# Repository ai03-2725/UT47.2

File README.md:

# UT47.2
Hot-swappable 40% Keyboard PCB

#### In light of recent claims that I am 100% liable for any of my open source PCBs, I am adding this disclaimer.
#### I provide these PCBs as a reference for designing keyboard PCBs. Using them within your projects will require a will to do research of one's own and to learn the workings of them, potentially fixing issues if they exist.
# I provide these PCBs without liability and without any guarantees regarding functionality, as expressed in the MIT license under which all of these PCBs are licensed.

Keyboard Layout Editor layout: [Layout](http://www.keyboard-layout-editor.com/#/gists/ddc8fda154c2c93ac26e38cd5da5988e)

An open-source commission for [KeyHive](https://keyhive.xyz/).

The design is inspired by 40percent.club's Gnap keyboard, which is licensed under [CC BY-SA 4.0](https://creativecommons.org/licenses/by-sa/4.0/).

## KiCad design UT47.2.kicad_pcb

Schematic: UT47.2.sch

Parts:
C1, C2: 22p; C_0603
C3: 1uF; C_0603
C4, C5: 0.1u; C_0603
C6: 4.7u; C_0603
CR1, CR2, CR3, CR4, CR5, CR6, CR7, CR8: 0.1u; C_0603
F1: 500mA; Fuse_SMD1206_Reflow
R1, R5: 10k; R_0603
R2, R3: 22; R_0603
R4, R6: 5.1k; R_0603
RGB1, RGB2, RGB3, RGB4, RGB5, RGB6, RGB7, RGB8: WS2812B
SW1: SW_PUSH; SKQG-1155865
U1: ATMEGA32U2-AU; QFN-32-1EP_5x5mm_Pitch0.5mm
U2: PRTR5V0U2X; SOT143B
USB1: HRO-TYPE-C-31-M-12; HRO-TYPE-C-31-M-12-Assembly
Y1: 16MHz; Crystal_SMD_3225-4pin_3.2x2.5mm

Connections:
+5V: C4.1, C5.1, C6.1, CR1.1, CR2.1, CR3.1, CR4.1, CR5.1, CR6.1, CR7.1, CR8.1, F1.1, R1.1, RGB1.1 (VCC), RGB2.1 (VCC), RGB3.1 (VCC), RGB4.1 (VCC), RGB5.1 (VCC), RGB6.1 (VCC), RGB7.1 (VCC), RGB8.1 (VCC), U1.4 (VCC), U1.31 (UVCC), U1.32 (AVCC)
COL0: U1.26 ((PCINT10)PC4); also elsewhere on the board
COL1: U1.25 ((PCINT9/OC.1B)PC5); also elsewhere on the board
COL2: U1.21 ((PCINT7/OC.0A/OC.1C)PB7); also elsewhere on the board
COL3: U1.20 ((PCINT6)PB6); also elsewhere on the board
COL4: U1.19 ((PCINT5)PB5); also elsewhere on the board
COL5: U1.18 ((T1/PCINT4)PB4); also elsewhere on the board
COL6: U1.17 ((PD0/MISO/PCINT3)PB3); also elsewhere on the board
COL7: U1.16 ((PDI/MOSI/PCINT2)PB2); also elsewhere on the board
COL8: U1.15 ((SCLK/PCINT1)PB1); also elsewhere on the board
COL9: U1.14 ((~SS~/PCINT0)PB0); also elsewhere on the board
COL10: U1.12 ((~RTS~/AIN5/INT6)PD6); also elsewhere on the board
COL11: U1.11 ((XCK/AIN4/PCINT12)PD5); also elsewhere on the board
D+: R3.2, U1.29 (D+)
D-: R2.1, U1.30 (D-)
GND: C1.2, C2.2, C3.2, C4.2, C5.2, C6.2, CR1.2, CR2.2, CR3.2, CR4.2, CR5.2, CR6.2, CR7.2, CR8.2, R4.2, R5.1, R6.2, RGB1.3 (GND), RGB2.3 (GND), RGB3.3 (GND), RGB4.3 (GND), RGB5.3 (GND), RGB6.3 (GND), RGB7.3 (GND), RGB8.3 (GND), SW1.1, U1.3 (GND), U1.28 (UGND), U2.1, USB1.1, USB1.12, USB1.13, Y1.2, Y1.4
unnamed: C1.1, U1.1 (XTAL1), Y1.1
unnamed: C2.1, U1.2 (PC0(XTAL2)), Y1.3
unnamed: C3.1, U1.27 (UCAP)
unnamed: R1.2, SW1.2, U1.24 (PC1(~RESET~/dW))
unnamed: R2.2, U2.3, USB1.5, USB1.7
unnamed: R3.1, U2.2, USB1.6, USB1.8
unnamed: R4.1, USB1.10
unnamed: R5.2, U1.13 ((~CTS~/~HWB~/AIN6/T0/INT7)PD7)
unnamed: R6.1, USB1.4
unnamed: RGB1.2 (DOUT), RGB2.4 (DIN)
unnamed: RGB2.2 (DOUT), RGB3.4 (DIN)
unnamed: RGB3.2 (DOUT), RGB4.4 (DIN)
unnamed: RGB4.2 (DOUT), RGB5.4 (DIN)
unnamed: RGB5.2 (DOUT), RGB6.4 (DIN)
unnamed: RGB6.2 (DOUT), RGB7.4 (DIN)
unnamed: RGB7.2 (DOUT), RGB8.4 (DIN)
RGBLED: RGB1.4 (DIN), U1.23 ((OC.1A/PCINT8)PC6)
ROW0: U1.7 ((AIN0/INT1)PD1); also elsewhere on the board
ROW1: U1.8 ((RXD1/AIN1/INT2)PD2); also elsewhere on the board
ROW2: U1.9 ((TXD1/INT3)PD3); also elsewhere on the board
ROW3: U1.10 ((INT5/AIN3)PD4); also elsewhere on the board
VCC: F1.2, U2.4, USB1.2, USB1.11

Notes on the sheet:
Mir Keyboard
2018-11-28
1.0

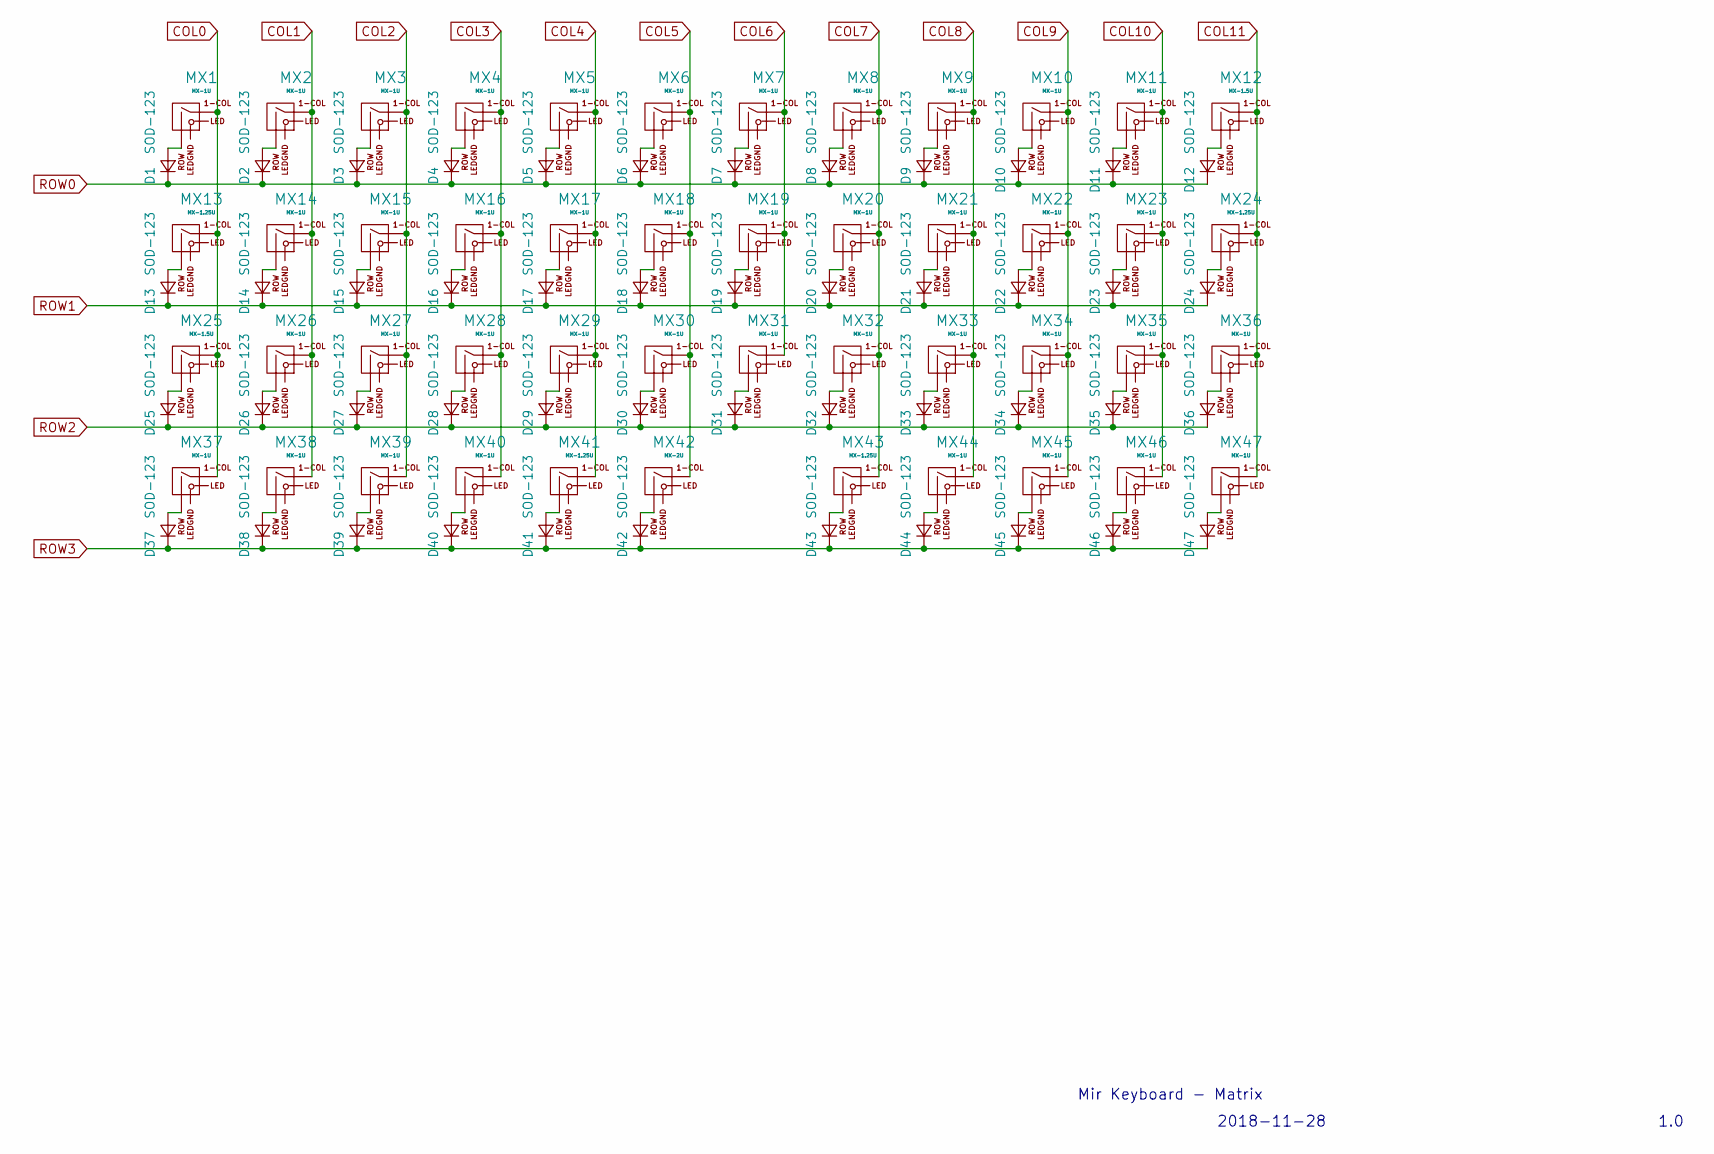
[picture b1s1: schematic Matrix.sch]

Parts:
D1, D2, D3, D4, D5, D6, D7, D8, D9, D10, D11, D12, D13, D14, D15, D16, D17, D18, D19, D20, D21, D22, D23, D24, D25, D26, D27, D28, D29, D30, D31, D32, D33, D34, D35, D36, D37, D38, D39, D40, D41, D42, D43, D44, D45, D46, D47: SOD-123; D_SOD-123
MX1, MX2, MX3, MX4, MX5, MX6, MX7, MX8, MX9, MX10, MX11, MX14, MX15, MX16, MX17, MX18, MX19, MX20, MX21, MX22, MX23, MX26, MX27, MX28, MX29, MX30, MX31, MX32, MX33, MX34, MX35, MX36, MX37, MX38, MX39, MX40, MX44, MX45, MX46, MX47: MX-1U; MXOnly-1U-Hotswap
MX12, MX25: MX-1.5U; MXOnly-1.5U-Hotswap
MX13, MX24, MX41, MX43: MX-1.25U; MXOnly-1.25U-Hotswap
MX42: MX-2U; MXOnly-2U-Hotswap-ReversedStabilizers

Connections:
COL0: MX1.1 (COL), MX13.1 (COL), MX25.1 (COL), MX37.1 (COL); also elsewhere on the board
COL1: MX2.1 (COL), MX14.1 (COL), MX26.1 (COL), MX38.1 (COL); also elsewhere on the board
COL2: MX3.1 (COL), MX15.1 (COL), MX27.1 (COL), MX39.1 (COL); also elsewhere on the board
COL3: MX4.1 (COL), MX16.1 (COL), MX28.1 (COL), MX40.1 (COL); also elsewhere on the board
COL4: MX5.1 (COL), MX17.1 (COL), MX29.1 (COL), MX41.1 (COL); also elsewhere on the board
COL5: MX6.1 (COL), MX18.1 (COL), MX30.1 (COL), MX42.1 (COL); also elsewhere on the board
COL6: MX7.1 (COL), MX19.1 (COL), MX31.1 (COL); also elsewhere on the board
COL7: MX8.1 (COL), MX20.1 (COL), MX32.1 (COL), MX43.1 (COL); also elsewhere on the board
COL8: MX9.1 (COL), MX21.1 (COL), MX33.1 (COL), MX44.1 (COL); also elsewhere on the board
COL9: MX10.1 (COL), MX22.1 (COL), MX34.1 (COL), MX45.1 (COL); also elsewhere on the board
COL10: MX11.1 (COL), MX23.1 (COL), MX35.1 (COL), MX46.1 (COL); also elsewhere on the board
COL11: MX12.1 (COL), MX24.1 (COL), MX36.1 (COL), MX47.1 (COL); also elsewhere on the board
unnamed: D1.2 (A), MX1.2 (ROW)
unnamed: D2.2 (A), MX2.2 (ROW)
unnamed: D3.2 (A), MX3.2 (ROW)
unnamed: D4.2 (A), MX4.2 (ROW)
unnamed: D5.2 (A), MX5.2 (ROW)
unnamed: D6.2 (A), MX6.2 (ROW)
unnamed: D7.2 (A), MX7.2 (ROW)
unnamed: D8.2 (A), MX8.2 (ROW)
unnamed: D9.2 (A), MX9.2 (ROW)
unnamed: D10.2 (A), MX10.2 (ROW)
unnamed: D11.2 (A), MX11.2 (ROW)
unnamed: D12.2 (A), MX12.2 (ROW)
unnamed: D13.2 (A), MX13.2 (ROW)
unnamed: D14.2 (A), MX14.2 (ROW)
unnamed: D15.2 (A), MX15.2 (ROW)
unnamed: D16.2 (A), MX16.2 (ROW)
unnamed: D17.2 (A), MX17.2 (ROW)
unnamed: D18.2 (A), MX18.2 (ROW)
unnamed: D19.2 (A), MX19.2 (ROW)
unnamed: D20.2 (A), MX20.2 (ROW)
unnamed: D21.2 (A), MX21.2 (ROW)
unnamed: D22.2 (A), MX22.2 (ROW)
unnamed: D23.2 (A), MX23.2 (ROW)
unnamed: D24.2 (A), MX24.2 (ROW)
unnamed: D25.2 (A), MX25.2 (ROW)
unnamed: D26.2 (A), MX26.2 (ROW)
unnamed: D27.2 (A), MX27.2 (ROW)
unnamed: D28.2 (A), MX28.2 (ROW)
unnamed: D29.2 (A), MX29.2 (ROW)
unnamed: D30.2 (A), MX30.2 (ROW)
unnamed: D31.2 (A), MX31.2 (ROW)
unnamed: D32.2 (A), MX32.2 (ROW)
unnamed: D33.2 (A), MX33.2 (ROW)
unnamed: D34.2 (A), MX34.2 (ROW)
unnamed: D35.2 (A), MX35.2 (ROW)
unnamed: D36.2 (A), MX36.2 (ROW)
unnamed: D37.2 (A), MX37.2 (ROW)
unnamed: D38.2 (A), MX38.2 (ROW)
unnamed: D39.2 (A), MX39.2 (ROW)
unnamed: D40.2 (A), MX40.2 (ROW)
unnamed: D41.2 (A), MX41.2 (ROW)
unnamed: D42.2 (A), MX42.2 (ROW)
unnamed: D43.2 (A), MX43.2 (ROW)
unnamed: D44.2 (A), MX44.2 (ROW)
unnamed: D45.2 (A), MX45.2 (ROW)
unnamed: D46.2 (A), MX46.2 (ROW)
unnamed: D47.2 (A), MX47.2 (ROW)
ROW0: D1.1 (K), D2.1 (K), D3.1 (K), D4.1 (K), D5.1 (K), D6.1 (K), D7.1 (K), D8.1 (K), D9.1 (K), D10.1 (K), D11.1 (K), D12.1 (K); also elsewhere on the board
ROW1: D13.1 (K), D14.1 (K), D15.1 (K), D16.1 (K), D17.1 (K), D18.1 (K), D19.1 (K), D20.1 (K), D21.1 (K), D22.1 (K), D23.1 (K), D24.1 (K); also elsewhere on the board
ROW2: D25.1 (K), D26.1 (K), D27.1 (K), D28.1 (K), D29.1 (K), D30.1 (K), D31.1 (K), D32.1 (K), D33.1 (K), D34.1 (K), D35.1 (K), D36.1 (K); also elsewhere on the board
ROW3: D37.1 (K), D38.1 (K), D39.1 (K), D40.1 (K), D41.1 (K), D42.1 (K), D43.1 (K), D44.1 (K), D45.1 (K), D46.1 (K), D47.1 (K); also elsewhere on the board

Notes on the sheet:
Mir Keyboard - Matrix
2018-11-28
1.0

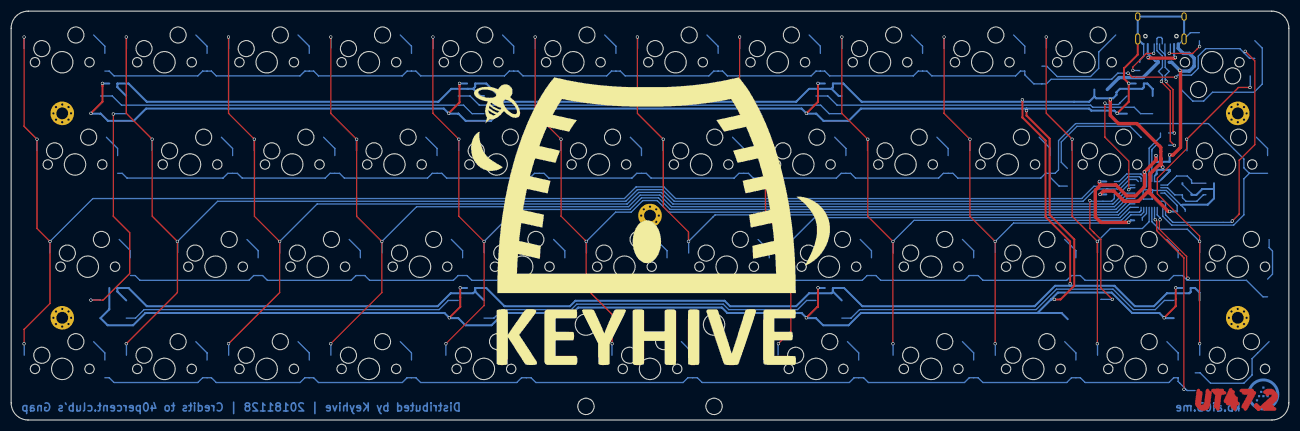
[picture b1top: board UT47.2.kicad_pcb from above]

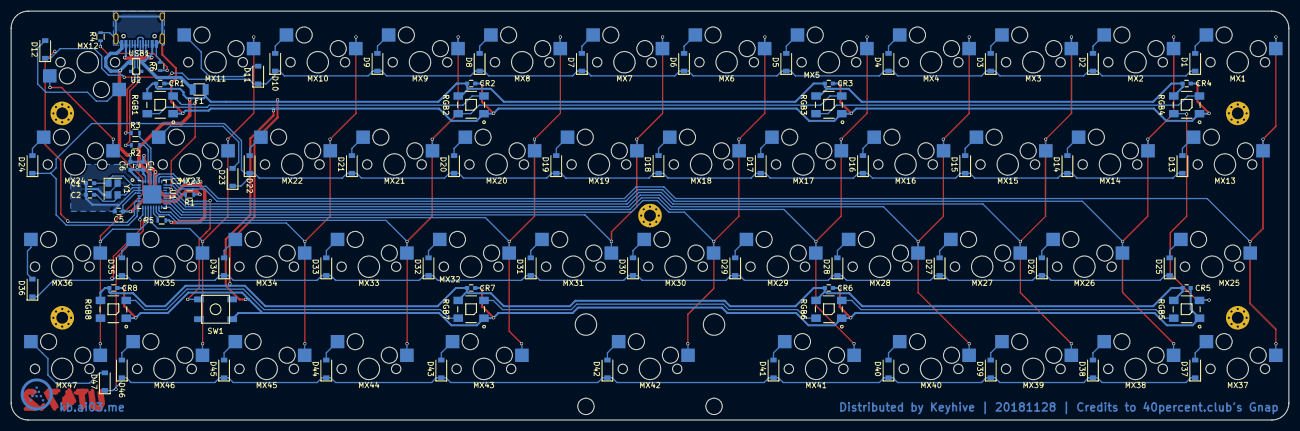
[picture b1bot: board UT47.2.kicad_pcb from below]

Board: 2 copper layers, 238.1 x 76.2 mm, 128 parts (81 on the bottom side), 85 nets.

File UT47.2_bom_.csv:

Component,Description,Part,References,Value,Footprint,Quantity Per PCB,Datasheet
1,Unpolarized capacitor,C_Small,C4 C5 CR1 CR2 CR3 CR4 CR5 CR6 CR7 CR8,0.1u,C_0603,10,
2,Unpolarized capacitor,C_Small,C3,1uF,C_0603,1,
3,Unpolarized capacitor,C_Small,C1 C2,22p,C_0603,2,
4,Unpolarized capacitor,C_Small,C6,4.7u,C_0603,1,
5,"Diode, small symbol",D_Small,D1 D2 D3 D4 D5 D6 D7 D8 D9 D10 D11 D12 D13 D14 D15 D16 D17 D18 D19 D20 D21 D22 D23 D24 D25 D26 D27 D28 D29 D30 D31 D32 D33 D34 D35 D36 D37 D38 D39 D40 D41 D42 D43 D44 D45 D46 D47,SOD-123,D_SOD-123,47,~
6,"resettable fuse, polymeric positive temperature coefficient (PPTC), small symbol",Polyfuse_Small,F1,500mA,Fuse_SMD1206_Reflow,1,
7,,MX-1U,MX13 MX24 MX41 MX43,MX-1.25U,MXOnly-1.25U-Hotswap,4,
8,,MX-1U,MX12 MX25,MX-1.5U,MXOnly-1.5U-Hotswap,2,
9,,MX-1U,MX1 MX2 MX3 MX4 MX5 MX6 MX7 MX8 MX9 MX10 MX11 MX14 MX15 MX16 MX17 MX18 MX19 MX20 MX21 MX22 MX23 MX26 MX27 MX28 MX29 MX30 MX31 MX32 MX33 MX34 MX35 MX36 MX37 MX38 MX39 MX40 MX44 MX45 MX46 MX47,MX-1U,MXOnly-1U-Hotswap,40,
10,,MX-1U,MX42,MX-2U,MXOnly-2U-Hotswap-ReversedStabilizers,1,
11,"Resistor, small symbol",R_Small,R1 R5,10k,R_0603,2,
12,"Resistor, small symbol",R_Small,R2 R3,22,R_0603,2,
13,"Resistor, small symbol",R_Small,R4 R6,5.1k,R_0603,2,
14,,WS2812B,RGB1 RGB2 RGB3 RGB4 RGB5 RGB6 RGB7 RGB8,WS2812B,WS2812B,8,
15,,SW_PUSH,SW1,SW_PUSH,SKQG-1155865,1,
16,,ATMEGA32U2-AU,U1,ATMEGA32U2-AU,QFN-32-1EP_5x5mm_Pitch0.5mm,1,http://www.atmel.com/Images/doc7799.pdf
17,,PRTR5V0U2X,U2,PRTR5V0U2X,SOT143B,1,
18,,HRO-TYPE-C-31-M-12,USB1,HRO-TYPE-C-31-M-12,HRO-TYPE-C-31-M-12-Assembly,1,
19,"Four pin crystal, two ground/package pins (pin2 and 4) small symbol",Crystal_GND24_Small,Y1,16MHz,Crystal_SMD_3225-4pin_3.2x2.5mm,1,
,,,,,,,
,,,,,,,
,,,,,,,
,,,,,,,
,,,,,,,
Component Groups:,19,,,,,,
Component Count:,128,,,,,,
Fitted Components:,128,,,,,,
Number of PCBs:,1,,,,,,
Total components:,128,,,,,,
Schematic Version:,,,,,,,
Schematic Date:,,,,,,,
BoM Date:,11/28/2018 21:01,,,,,,
Schematic Source:,UT47.2.sch,,,,,,
KiCad Version:,Eeschema (5.0.0),,,,,,

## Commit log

2018-11-29 Add necessary files based on Voyager 60:
2018-11-29 Update to kicad5
2018-11-29 Update submodules
2018-11-29 Add more hotswap sizes
2018-11-29 Route without MCU connections
2018-11-29 Finish routing
2018-11-29 Decorations
2018-11-29 Error check
2018-11-29 Add corner indicators for RGBs
2018-11-29 Rename project
2018-11-29 Fix position files
2018-11-29 Final tweaks
2018-11-29 Finally get KiCad to print properly
2018-11-29 Partially complete production data
2018-11-29 Finish production spreadsheet
2018-11-29 Push render
2018-11-29 Add render
2018-11-29 Adjust a bit of silkscreen
2019-01-06 Annotate overall dimensions in mm
2019-01-07 Build generic case files
2019-01-29 Update with drill holes
2019-01-29 New case data
2019-01-29 Rename gerber

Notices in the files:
README.md:
Creative Commons Attribution-ShareAlike 4.0 International License
